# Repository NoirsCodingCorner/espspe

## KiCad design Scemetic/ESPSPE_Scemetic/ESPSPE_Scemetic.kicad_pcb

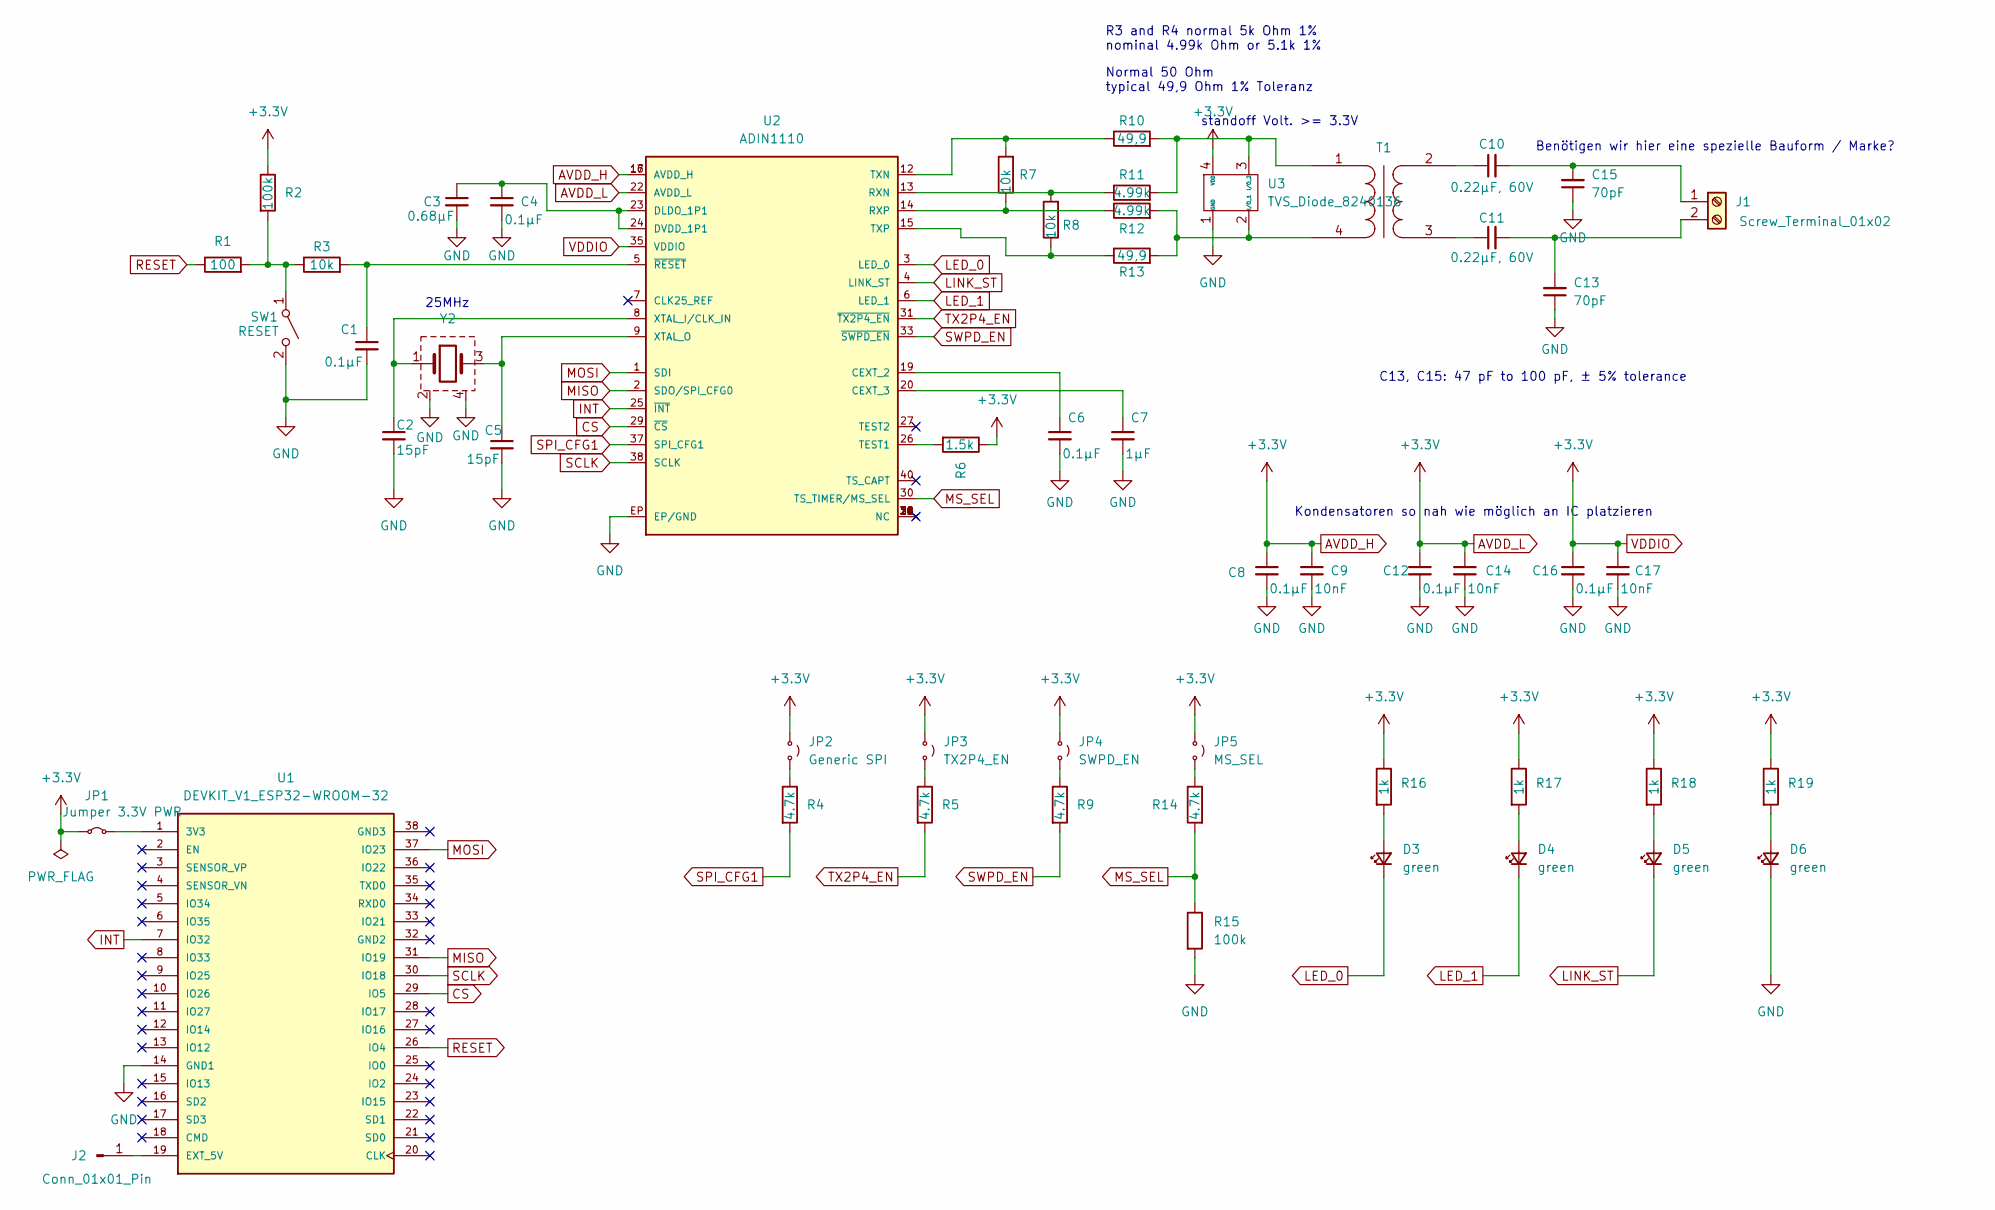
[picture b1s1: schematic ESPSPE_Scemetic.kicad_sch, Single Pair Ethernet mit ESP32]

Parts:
C1, C4, C6, C8, C12, C16: 0.1µF; C_0805_2012Metric_Pad1.18x1.45mm_HandSolder
C2, C5: 15pF; C_0805_2012Metric_Pad1.18x1.45mm_HandSolder
C3: 0.68µF; C_0805_2012Metric_Pad1.18x1.45mm_HandSolder
C7: 1µF; C_0805_2012Metric_Pad1.18x1.45mm_HandSolder
C9, C14, C17: 10nF; C_0805_2012Metric_Pad1.18x1.45mm_HandSolder
C10, C11: 0.22µF, 60V; C_0805_2012Metric_Pad1.18x1.45mm_HandSolder
C13, C15: 70pF; C_0805_2012Metric_Pad1.18x1.45mm_HandSolder
D3, D4, D5, D6: green; LED_0805_2012Metric_Pad1.15x1.40mm_HandSolder
J1: Screw_Terminal_01x02; TerminalBlock_Phoenix_MPT-0,5-2-2.54_1x02_P2.54mm_Horizontal
J2: Conn_01x01_Pin; PinHeader_1x01_P2.54mm_Vertical
JP1: Jumper 3.3V PWR; PinHeader_1x02_P2.54mm_Vertical
JP2: Generic SPI; PinHeader_1x02_P2.54mm_Vertical
JP3: TX2P4_EN; PinHeader_1x02_P2.54mm_Vertical
JP4: SWPD_EN; PinHeader_1x02_P2.54mm_Vertical
JP5: MS_SEL; PinHeader_1x02_P2.54mm_Vertical
R1: 100; R_0805_2012Metric_Pad1.20x1.40mm_HandSolder
R2, R15: 100k; R_0805_2012Metric_Pad1.20x1.40mm_HandSolder
R3, R7, R8: 10k; R_0805_2012Metric_Pad1.20x1.40mm_HandSolder
R4, R5, R9, R14: 4.7k; R_0805_2012Metric_Pad1.20x1.40mm_HandSolder
R6: 1.5k; R_0805_2012Metric_Pad1.20x1.40mm_HandSolder
R10, R13: 49,9; R_0603_1608Metric_Pad0.98x0.95mm_HandSolder
R11, R12: 4.99k; R_0603_1608Metric_Pad0.98x0.95mm_HandSolder
R16, R17, R18, R19: 1k; R_0805_2012Metric_Pad1.20x1.40mm_HandSolder
SW1: RESET; SW_PUSH_6mm
T1: 749070010; T_Wurth_WE-SPE_749070010; Part Number 749070010
U1: DEVKIT_V1_ESP32-WROOM-32; MODULE_DEVKIT_V1_ESP32-WROOM-32; PARTREV N/A
U2: ADIN1110; LFCSP-40
U3: TVS_Diode_8240136
Y2: CFPX-180_830105863709; Y_Wurth_WE-XTAL_Quartz-CFPX-180; Part Number 830105863709

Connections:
AVDD_H: C8.1, C9.1, C12.1, C14.1, C16.1, C17.1, JP1.1 (A), JP2.1 (A), JP3.1 (A), JP4.1 (A), JP5.1 (A), R2.1, R6.1, R16.1, R17.1, R18.1, R19.1, U2.16 (AVDD_H), U2.17 (AVDD_H), U2.22 (AVDD_L), U2.35 (VDDIO), U3.4 (VDD)
CS: U1.29 (IO5), U2.29 (~CS)
GND: C1.2, C2.2, C3.2, C4.2, C5.2, C6.2, C7.2, C8.2, C9.2, C12.2, C13.1, C14.2, C15.1, C16.2, C17.2, D6.1 (K), R15.2, SW1.2 (B), U1.14 (GND1), U2.EP (EP/GND), U3.1 (GND), Y2.2 (GND), Y2.4 (GND1)
INT: U1.7 (IO32), U2.25 (~INT)
LED_0: D3.1 (K), U2.3 (LED_0)
LED_1: D4.1 (K), U2.6 (LED_1)
LINK_ST: D5.1 (K), U2.4 (LINK_ST)
MISO: U1.31 (IO19), U2.2 (SDO/SPI_CFG0)
MOSI: U1.37 (IO23), U2.1 (SDI)
MS_SEL: R14.2, R15.1, U2.30 (TS_TIMER/MS_SEL)
unnamed: C10.1, T1.2
unnamed: C11.1, T1.3
unnamed: D3.2 (A), R16.2
unnamed: D4.2 (A), R17.2
unnamed: D5.2 (A), R18.2
unnamed: D6.2 (A), R19.2
unnamed: C10.2, C15.2, J1.1
unnamed: C11.2, C13.2, J1.2
unnamed: J2.1, U1.19 (EXT_5V)
unnamed: JP1.2 (B), U1.1 (3V3)
unnamed: JP2.2 (B), R4.1
unnamed: JP3.2 (B), R5.1
unnamed: JP4.2 (B), R9.1
unnamed: JP5.2 (B), R14.1
unnamed: R1.2, R2.2, R3.1, SW1.1 (A)
unnamed: C6.1, U2.19 (CEXT_2)
unnamed: C7.1, U2.20 (CEXT_3)
unnamed: C3.1, C4.1, U2.23 (DLDO_1P1), U2.24 (DVDD_1P1)
unnamed: R8.2, R11.1, U2.13 (RXN)
unnamed: R7.1, R12.1, U2.14 (RXP)
unnamed: R6.2, U2.26 (TEST1)
unnamed: R7.2, R10.1, U2.12 (TXN)
unnamed: R8.1, R13.1, U2.15 (TXP)
unnamed: C2.1, U2.8 (XTAL_I/CLK_IN), Y2.1
unnamed: C5.1, U2.9 (XTAL_O), Y2.3
unnamed: C1.1, R3.2, U2.5 (~RESET)
unnamed: R12.2, R13.2, T1.4, U3.2 (I/O_1)
unnamed: R10.2, R11.2, T1.1, U3.3 (I/O_2)
RESET: R1.1, U1.26 (IO4)
SCLK: U1.30 (IO18), U2.38 (SCLK)
SPI_CFG1: R4.2, U2.37 (SPI_CFG1)
SWPD_EN: R9.2, U2.33 (~SWPD_EN)
TX2P4_EN: R5.2, U2.31 (~TX2P4_EN)

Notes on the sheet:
Kondensatoren so nah wie möglich an IC platzieren
Normal 50 Ohm typical 49,9 Ohm 1% Toleranz
25MHz
R3 and R4 normal 5k Ohm 1% nominal 4.99k Ohm or 5.1k 1%
standoff Volt. >= 3.3V
Benötigen wir hier eine spezielle Bauform / Marke?
C13, C15: 47 pF to 100 pF, ± 5% tolerance

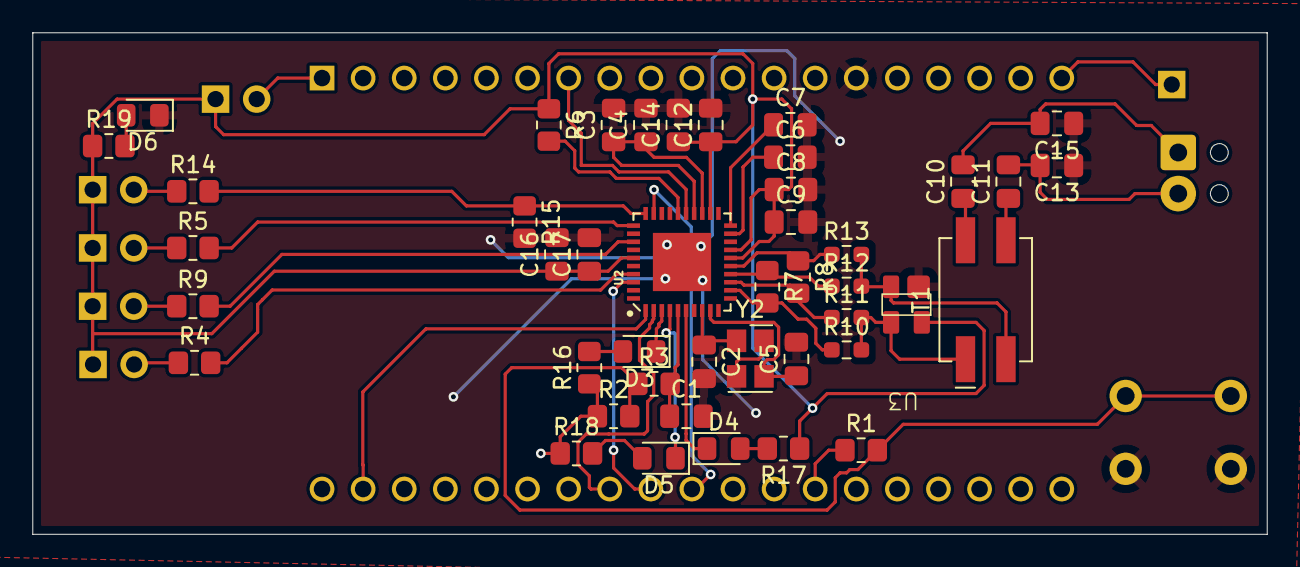
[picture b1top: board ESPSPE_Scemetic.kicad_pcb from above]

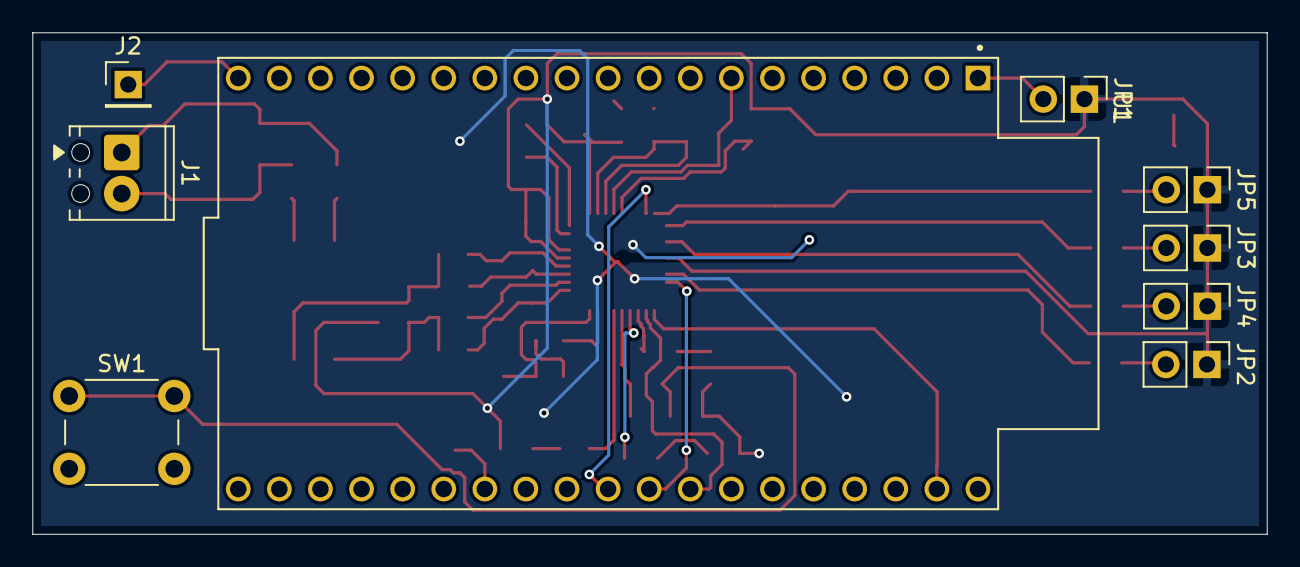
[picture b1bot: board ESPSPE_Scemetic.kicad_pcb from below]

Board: 2 copper layers, 76.3 x 31.0 mm, 53 parts (9 on the bottom side), 43 nets.

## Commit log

2025-11-02 I added a Pin Map; I added a KiCad Projekt with semetic, it's not finished yet; I added the adin1110 Datasheet with coments
2025-11-03 Add pwm_stresstest code
2025-11-03 pwmtest
2025-11-04 added ESP Pinout; Update of Scemetic -> should be ready to search for components
2025-11-11 Schaltplan vollständig
2025-11-11 Datenblatt mit Komentaren hinzugefügt
2025-11-11 Datenblatt von Transformator und Oszillator hinzugefügt
2025-11-11 Schaltplan Footprintzuweisung angefangen
2025-11-15 25MHz Oszillator hinzugefügt
2025-11-15 Jumper für PWR LED entfernt. Footprint für Traffo und Quartz zugewiesen. Z_Diode 0805 zugewiesen. Platine angefangen zu zeichen -> Bauteile angeordnet
2025-11-16 Jumper der LEDs entfernt
2025-11-16 Platine bis auf GND geroutet
2025-11-17 Z Dioden hinzugefügt
2025-11-17 Schönifizierung des Netzwerkes; Dioden THT zu SMD gewechselt
2025-11-25 Projekt Zip Hinzugefügt
2025-11-29 Platine Bauteile kompakter angeordnet
2025-11-29 Schutzdiode Hinzugefügt
2025-12-01 Vias eingefügt
2025-12-01 Bestellliste erstellt, Schaltplanänderung angepasst.
2025-12-16 Add: Datasheet and pinout
2025-12-16 Removed: Wrong Pinout andDatasheet
2025-12-16 Add: -ESP pinout -ESP Datasheet
2026-01-10 feat: initial commit of ADIN1110 driver skeleton and conference paper
2026-01-10 feat(presentation): overhaul UI design and add step-by-step navigation
2026-01-12 test(adin1110): Brute-Force SPI Protokoll-Scanner hinzugefügt
    - Implementiert Endlosschleife, die zwischen Open Alliance und Generic SPI wechselt
    - Fügt Software-Strapping hinzu, um MISO (CFG0) während des Resets auf High/Low zu zwingen
    - Dient zur Diagnose der MISO-Leitung und Überprüfung der Chip-Reaktion
    - Ermöglichte die Identifikation des fehlenden SCLK-Signals (via MISO Active-Low Verhalten)
2026-01-13 feat: add ADIN1110 forensic protocol scanner for hardware bring-up
2026-01-13 feat: Implement ADIN1110 diagnostics tool & Generic SPI driver
    This commit introduces a comprehensive diagnostic tool for the ADIN1110
    MAC-PHY to validate hardware connectivity and SPI communication.
    Key changes:
    - Implemented Generic SPI protocol driver (Mode 0) with CRC8 calculation.
    - Added MDIO bridge access to read internal PHY registers via MAC SPI.
    - Implemented polling mechanism for MDIO TRDONE (transaction done) bit.
2026-01-19 feat: Implementierung Packet-Engine und Register-Definitionen
2026-01-19 fix: end header
2026-01-19 fix: ADIN1110 Kommunikation repariert (Generic SPI + CRC + Padding)
2026-01-19 feat: fix SPI communication (enable HW-CRC & promiscuous mode)
    - Enable ADIN1110 CRC_APPEND (hardware FCS generation) to fix packet drops
    - Enable Promiscuous Mode to bypass strict MAC filtering
    - Optimize SPI transactions (DMA block transfer) to eliminate clock gaps
    - Verify stable link with correct payload reception
2026-01-21 feat: implement ADIN1110 driver skeleton based on ESP-IDF v5 architecture
    - Added generic SPI driver implementation with CRC8 support
    - Implemented MAC layer logic using esp_eth_mac_t interface
    - Created Dummy-PHY implementation to bypass MDIO requirement (ADIN1110 is MAC-PHY)
    - Fixed compilation issues related to ESP-IDF v5 breaking changes (process_frame)
    - Integrated driver into component structure
    - Verified build process with hello-world main
2026-01-22 feat(adin1110): implement robust driver framework with advanced diagnostics and SPI locking
    Body: Dieses Update transformiert den ADIN1110-Treiber in ein robustes Framework mit Fokus auf Stabilität, Fehlerdiagnose und korrekte LwIP-Anbindung. Auch wenn die vollständige Kommunikation (RX/TX)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
    1. MAC-Layer & Stabilität (adin_mac.c):
    Deep Research Fix (Stuck 0x80): Implementierung der hierarchischen IRQ-Löschung (PHY_SUBSYS / CRSM) zur Behebung des persistenten PHY-Interrupt-Zustands.
    Hybrid-Polling: Umstellung des RX-Tasks auf IRQ-Warten mit 50ms Timeout-Sicherheitsnetz zur Erhöhung der
2026-01-22 working blinking LED
2026-01-22 Presentationsready
2026-01-25 Paperplane
